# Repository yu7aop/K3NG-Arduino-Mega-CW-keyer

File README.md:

# K3NG-Arduino-Mega-CW-keyer
All you need for Arduino Mega 2560 CW keyer by K3NG
K3NG Winkeyer PCB for Arduino MEGA 2560. KEYER by Eagle software. 
PCB is toner-transfer method with hot Iron.  
If you are friendly with Eagle you can change footprints or schematic depends on your needs, or import in other software.

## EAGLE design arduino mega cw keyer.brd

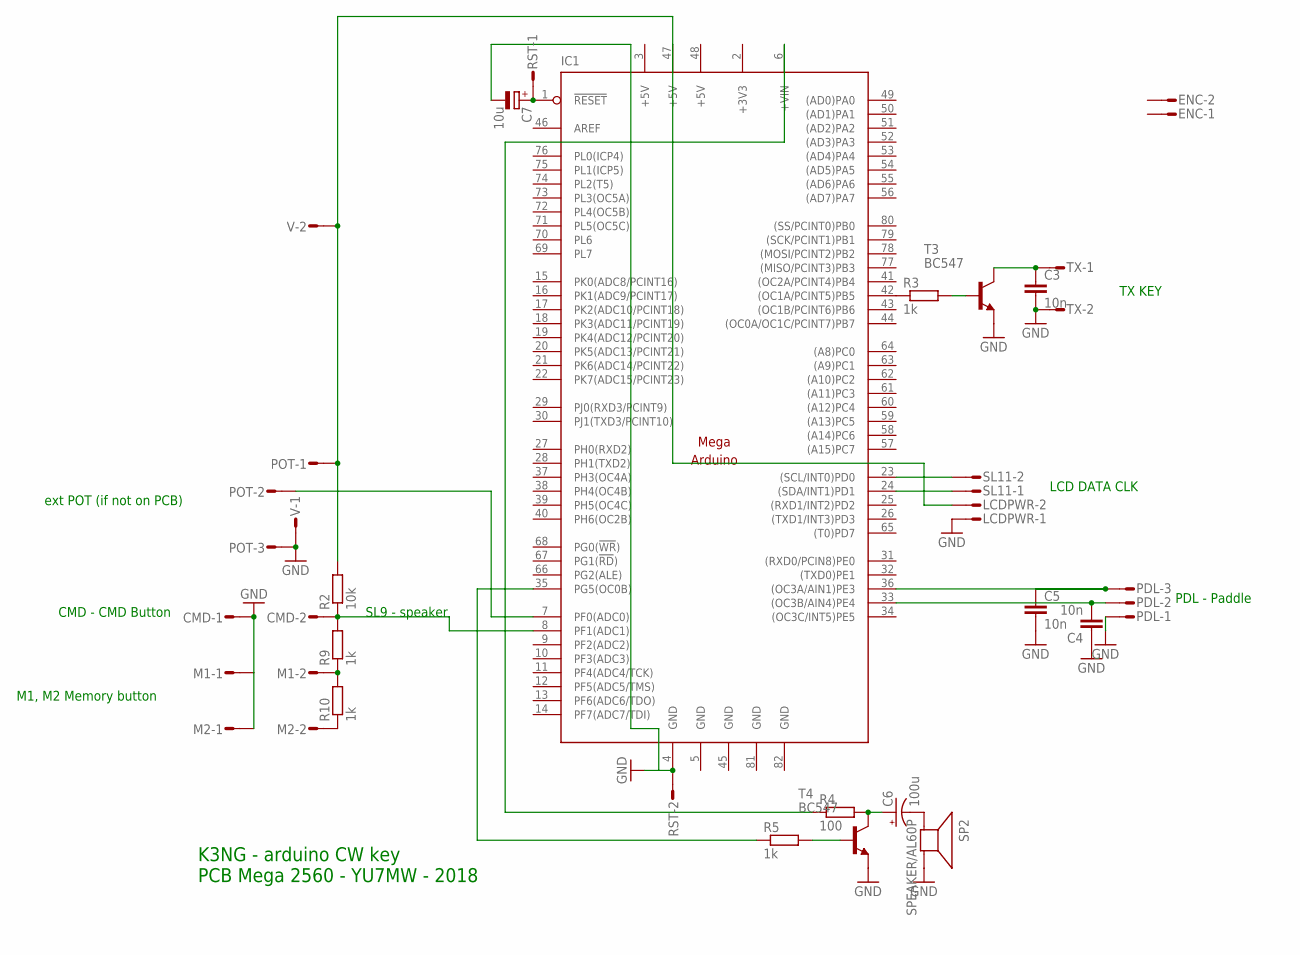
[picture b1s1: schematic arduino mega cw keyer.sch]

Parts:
C3, C4, C5: 10n; C050-025X075
C6: 100u; E2,5-5
C7: 10u; E2,5-6E
CMD: M02S; 02P
ENC: M02S; 02P
IC1: MEGAARDUINO_1; MEGA_ARDUINO
LCDPWR: M02S; 02P
M1, M2: M02S; 02P
PDL: M03S; 03P
POT: M03S; 03P
R2: 10k; 0207/10
R3, R5, R9, R10: 1k; 0207/10
R4: 100; 0207/10
RST: M02S; 02P
SL11: M02S; 02P
SP2: SPEAKER/AL60P; AL60P
T3, T4: BC547; TO92
TX: M02S; 02P
V: M02S; 02P

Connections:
+3V3: IC1.2 (+3V3)
+5V: IC1.3 (+5V), IC1.48 (+5V)
GND: C3.2, C4.1, C5.2, C7.-, CMD.1, IC1.4 (GND), IC1.5 (GND), IC1.45 (GND), IC1.81 (GND), IC1.82 (GND), LCDPWR.1, M1.1, M2.1, PDL.1, POT.3, RST.2, SP2.2 (-), T3.1 (E), T4.1 (E), TX.2, V.1
unnamed: IC1.7 (PF0(ADC0)), POT.2
unnamed: IC1.23 ((SCL/INT0)PD0), SL11.2
unnamed: IC1.24 ((SDA/INT1)PD1), SL11.1
unnamed: IC1.42 ((OC1A/PCINT5)PB5), R3.1
unnamed: C7.+, IC1.1 (!RESET), RST.1
unnamed: C5.1, IC1.36 ((OC3A/AIN1)PE3), PDL.3
unnamed: C4.2, IC1.33 ((OC3B/AIN4)PE4), PDL.2
unnamed: R3.2, T3.2 (B)
unnamed: C3.1, T3.3 (C), TX.1
unnamed: R5.2, T4.2 (B)
unnamed: C6.+, R4.2, T4.3 (C)
unnamed: C6.-, SP2.1 (+)
unnamed: IC1.6 (+VIN), R4.1
unnamed: IC1.35 (PG5(OC0B)), R5.1
unnamed: CMD.2, IC1.8 (PF1(ADC1)), R2.1, R9.2
unnamed: M1.2, R9.1, R10.2
unnamed: M2.2, R10.1
unnamed: IC1.47 (+5V), LCDPWR.2, POT.1, R2.2, V.2

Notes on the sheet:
CMD - CMD Button
M1, M2 Memory button
ext POT (if not on PCB)
LCD DATA CLK
TX KEY
PDL - Paddle
SL9 - speaker
K3NG - arduino CW key PCB Mega 2560 - YU7MW - 2018

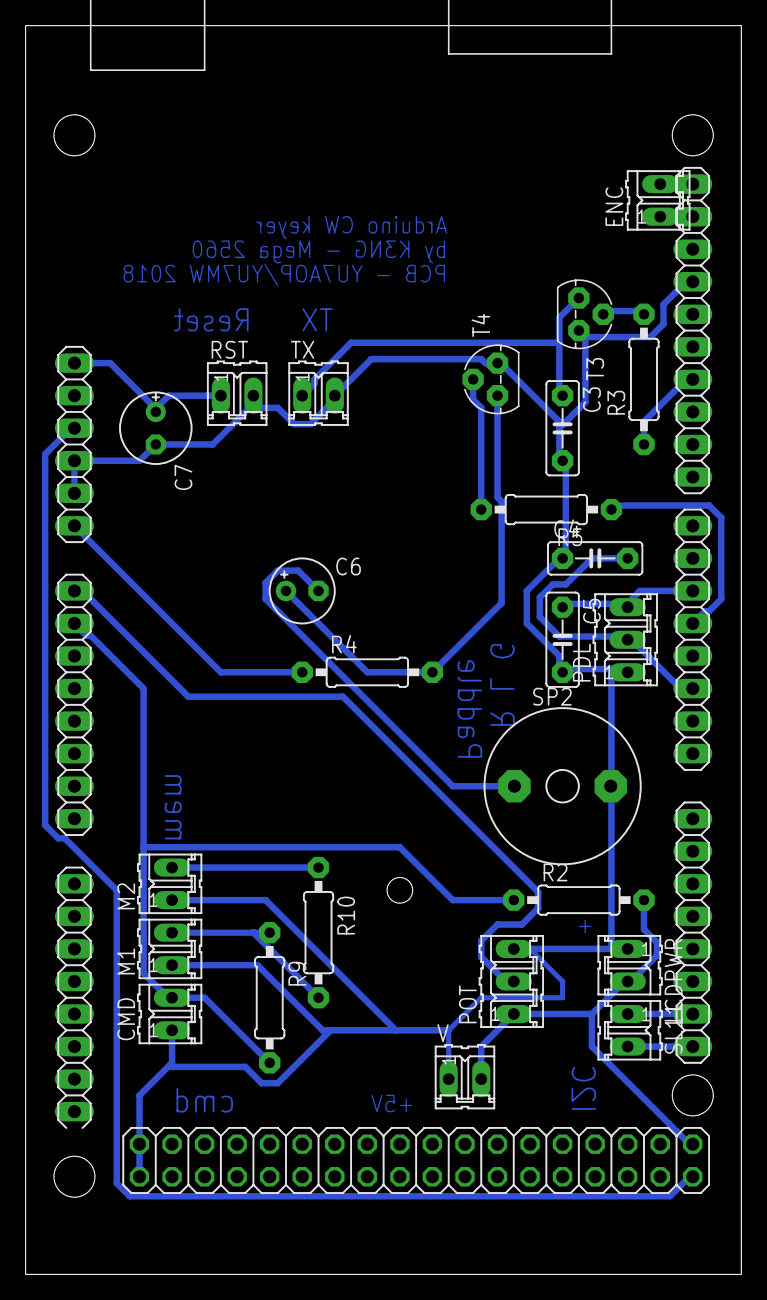
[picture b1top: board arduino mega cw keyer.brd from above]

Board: 2 copper layers, 55.9 x 97.5 mm, 26 parts (0 on the bottom side), 20 nets.

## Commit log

2018-11-06 Arduino Mega 2560 CW keyer
    K3NG Winkeyer PCB for Arduino MEGA 2560. KEYER by Eagle software. PCB is toner-transfer method with hot Iron.
    If you are friendly with Eagle you can change footprints or schematic depends on your needs, or import in other software.
